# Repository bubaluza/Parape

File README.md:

# Parape
PARAPE is a device developed for Project Class at UEPG (Universidade Estadual de Ponta Grossa - State University of Ponta Grossa).
The class proposes the students to develop and solve a real client problem using commercial and industrial standards from the documentation to the implementation.
PARAPE covers physiotherapeutic monitoring of the action of walk, alarming the user by pulsing a motor when they did the movement incorrectly while the device is attached to their legs;

The client in use was a kid with celebral palsy that walked wrong when not giving attention. The objective was to alert the user so they could remember to walk in the right way.

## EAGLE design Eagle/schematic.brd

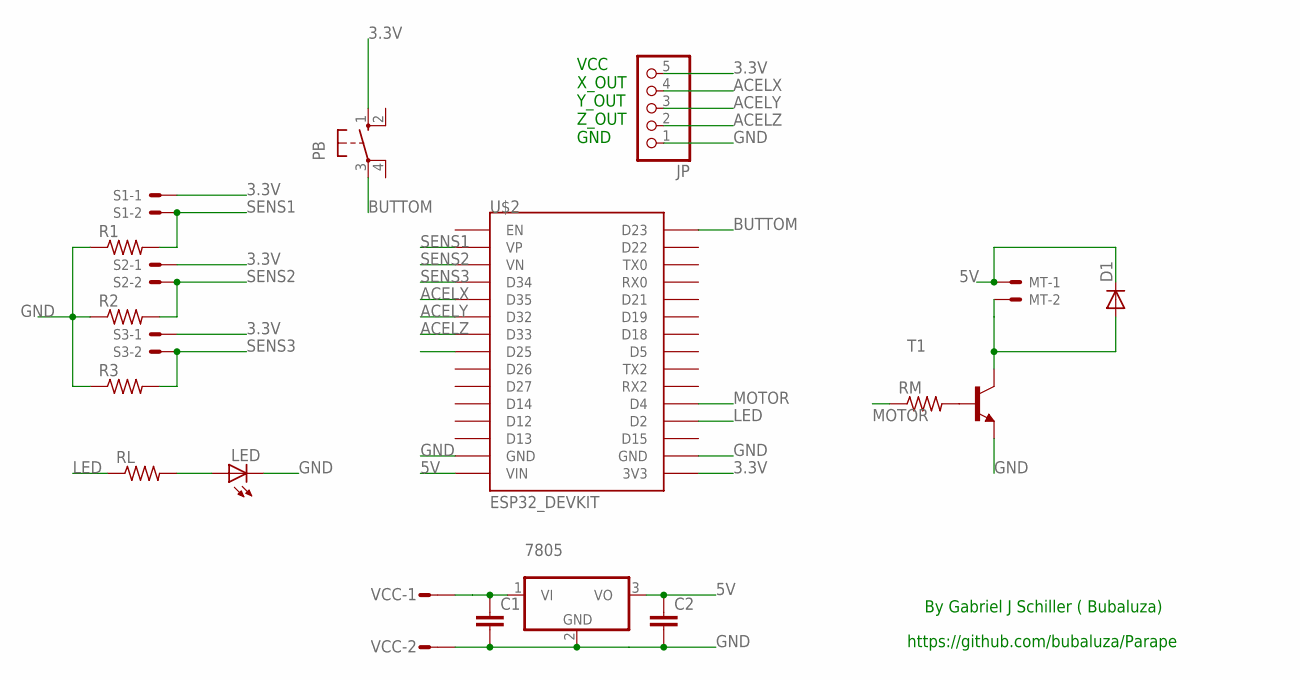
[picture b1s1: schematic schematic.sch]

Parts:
7805: 786TV; TO220V
C1, C2: C2,5-3; C2.5-3
D1: 1N4148DO35-10; DO35-10
JP: PINHD-1X5; 1X05
LED: LED5MM
MT: 332-02
PB: 10-XX; B3F-10XX
R1, R2, R3: R-US_0207/7; 0207/7
RL: R-US_0207/7; 0207/7
RM: R-US_0207/7; 0207/7
S1, S2, S3: 332-02
T1: 2N2222; TO18
U$2: ESP32_DEVKIT
VCC: L02P

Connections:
3.3V: JP.5, PB.1 (S), S1.1, S2.1, S3.1, U$2.3V3
5V: 7805.3 (VO), C2.1, D1.C, MT.1, U$2.VIN
ACELX: JP.4, U$2.D35
ACELY: JP.3, U$2.D32
ACELZ: JP.2, U$2.D33
BUTTOM: PB.3, U$2.D23
GND: 7805.2 (GND), C1.2, C2.2, JP.1, LED.K (C), R1.1, R2.1, R3.1, T1.1 (E), U$2.GND@1 (GND), U$2.GND@2 (GND), VCC.2
LED: RL.1, U$2.D2
MOTOR: RM.1, U$2.D4
unnamed: 7805.1 (VI), C1.1, VCC.1
unnamed: RM.2, T1.2 (B)
unnamed: D1.A, MT.2, T1.3 (C)
unnamed: LED.A, RL.2
SENS1: R1.2, S1.2, U$2.VP
SENS2: R2.2, S2.2, U$2.VN
SENS3: R3.2, S3.2, U$2.D34

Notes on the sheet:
VCC X_OUT Y_OUT Z_OUT GND
By Gabriel J Schiller ( Bubaluza)
https://github.com/bubaluza/Parape

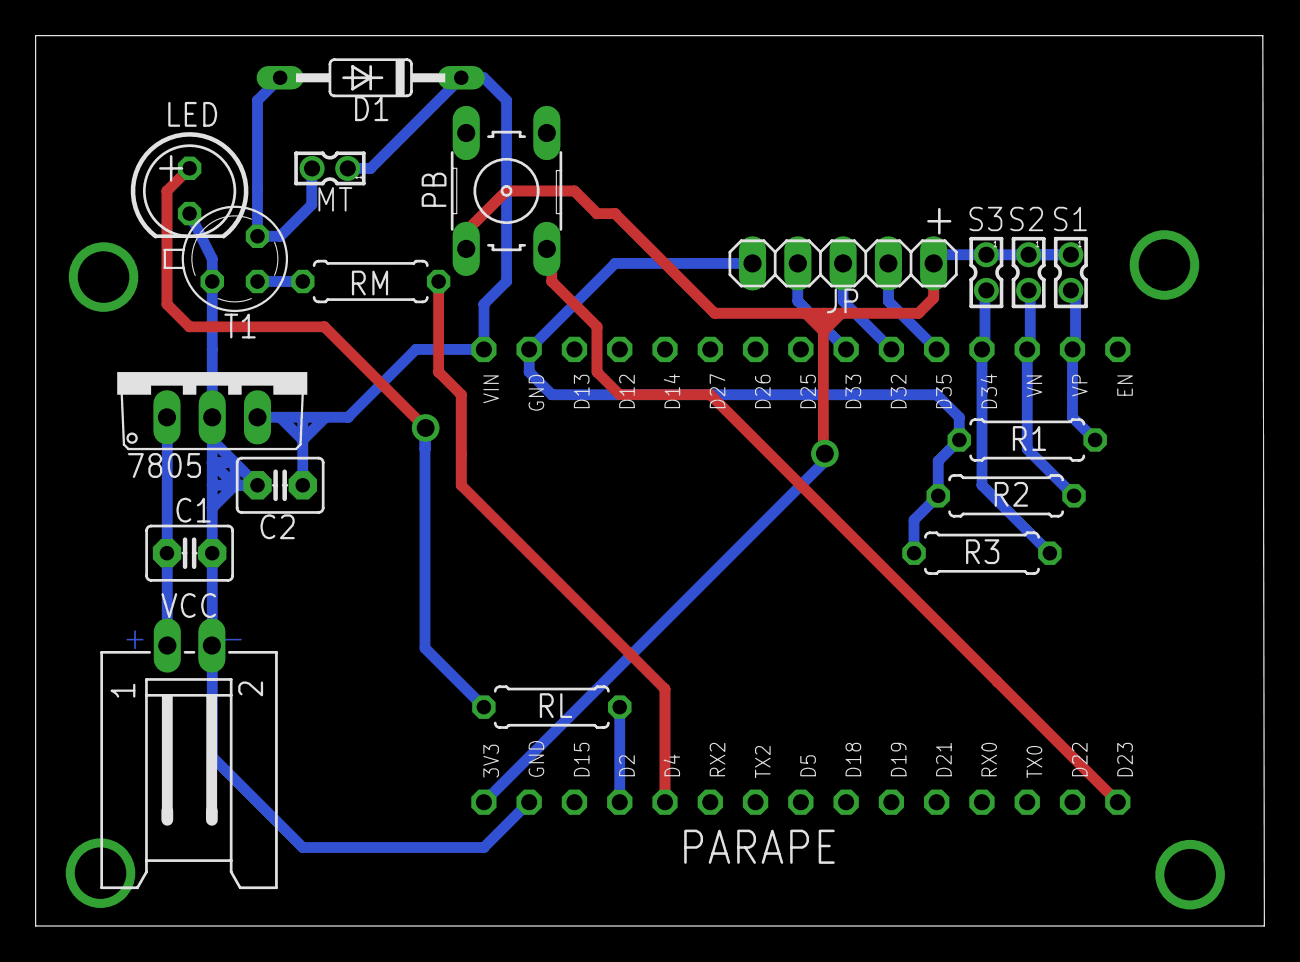
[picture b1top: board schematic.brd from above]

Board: 2 copper layers, 68.9 x 49.9 mm, 19 parts (0 on the bottom side), 16 nets.

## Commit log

2018-11-20 Create programParape
2018-11-20 Rename programParape to programParape.ino
2018-11-20 html buttom, processor buttom, time update,
2018-11-21 html update, perfect walk update, name change
2018-11-21 right File
2018-11-22 fix meio>calcanhar
2018-11-22 b4 last updates
2018-11-29 English Update
2018-12-04 I2c acc
2018-12-10 accel mean fix
2018-12-13 new webpage config
2018-12-21 doc improve
